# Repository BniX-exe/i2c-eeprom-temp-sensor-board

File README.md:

I2C EEPROM & Sensor Board
A custom 2-layer PCB designed in KiCad, integrating I²C-based memory, temperature sensing, elapsed time recording, and power regulation.
Overview
This project demonstrates schematic design, component selection, PCB layout, and integration of multiple I²C peripherals on a compact board.
The PCB was recreated as a personal portfolio project based on hardware design experience gained during an engineering internship.
Hardware Components
Component
Description
AT24C501
I²C EEPROM
TMP102
Digital temperature sensor
DS1683S+
Elapsed time recorder
AP2204K-ADJ
Adjustable LDO voltage regulator
Schottky Diode
Input reverse-current protection
LED
Alarm status indication
Design Features
	•	2-layer PCB designed using KiCad
	•	5V input and regulated 3.3V supply
	•	Shared I²C communication bus
	•	4.7kΩ I²C pull-up resistors
	•	On-board decoupling capacitors
	•	2×5 external interface connector
	•	Alarm and event signal connections
PCB Design
Schematic

PCB Layout

Design Tools
	•	KiCad — Schematic Capture
	•	KiCad PCB Editor — PCB Layout and Routing
Project Status
PCB schematic and layout completed. Physical manufacturing and hardware validation have not been documented.
Note
This repository contains a personally recreated PCB design intended for educational and portfolio purposes.

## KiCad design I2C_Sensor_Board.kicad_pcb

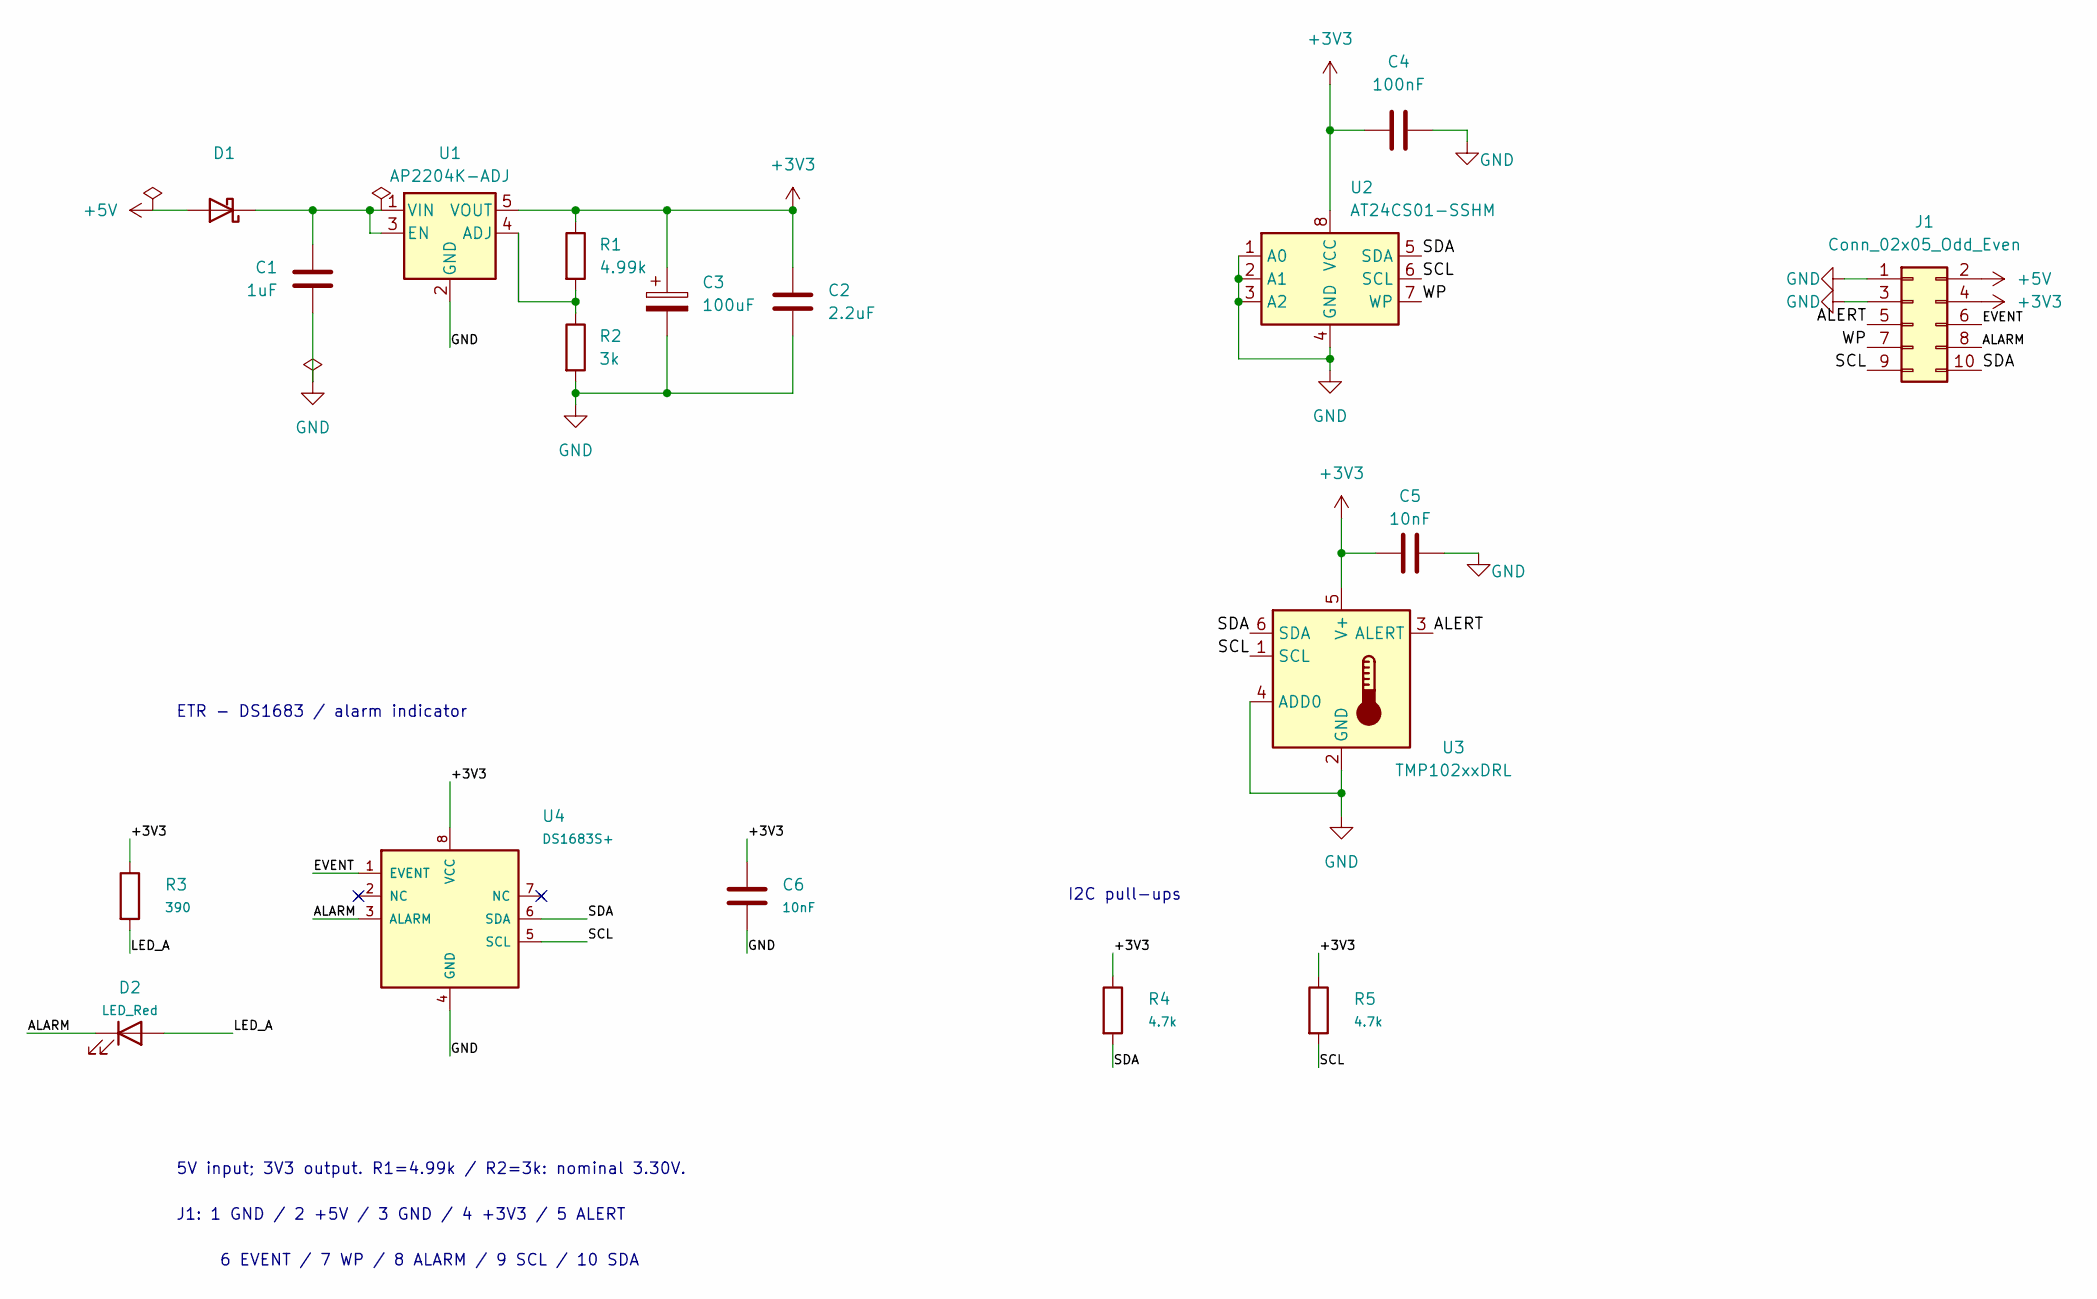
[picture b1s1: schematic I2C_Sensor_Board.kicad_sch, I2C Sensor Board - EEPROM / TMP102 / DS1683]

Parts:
C1: 1uF; C_1206_3216Metric
C2: 2.2uF; C_1206_3216Metric
C3: 100uF; CP_EIA-3528-21_Kemet-B
C4: 100nF; C_0402_1005Metric
C5, C6: 10nF; C_0402_1005Metric
D1: D_1206_3216Metric
D2: LED_Red; LED_0603_1608Metric
J1: Conn_02x05_Odd_Even; PinHeader_2x05_P2.54mm_Vertical
R1: 4.99k; R_0402_1005Metric
R2: 3k; R_0402_1005Metric
R3: 390; R_0402_1005Metric
R4, R5: 4.7k; R_0402_1005Metric
U1: AP2204K-ADJ; SOT-23-5
U2: AT24CS01-SSHM; SOIC-8_3.9x4.9mm_P1.27mm
U3: TMP102xxDRL; SOT-563
U4: DS1683S+; SOIC-8_3.9x4.9mm_P1.27mm

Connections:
+3V3: C2.1, C3.1, C4.1, C5.1, C6.1, J1.4, R1.1, R3.1, R4.1, R5.1, U1.5 (VOUT), U2.8 (VCC), U3.5 (V+), U4.8 (VCC)
+5V: D1.2 (A), J1.2
/ALARM: D2.1 (K), J1.8, U4.3 (ALARM)
/ALERT: J1.5, U3.3 (ALERT)
/EVENT: J1.6, U4.1 (EVENT)
/LED_A: D2.2 (A), R3.2
/SCL: J1.9, R5.2, U2.6 (SCL), U3.1 (SCL), U4.5 (SCL)
/SDA: J1.10, R4.2, U2.5 (SDA), U3.6 (SDA), U4.6 (SDA)
/WP: J1.7, U2.7 (WP)
GND: C1.2, C2.2, C3.2, C4.2, C5.2, C6.2, J1.1, J1.3, R2.2, U1.2 (GND), U2.1 (A0), U2.2 (A1), U2.3 (A2), U2.4 (GND), U3.2 (GND), U3.4 (ADD0), U4.4 (GND)
unnamed: C1.1, D1.1 (K), U1.1 (VIN), U1.3 (EN)
unnamed: R1.2, R2.1, U1.4 (ADJ)

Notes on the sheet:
5V input; 3V3 output. R1=4.99k / R2=3k: nominal 3.30V.
J1: 1 GND / 2 +5V / 3 GND / 4 +3V3 / 5 ALERT
6 EVENT / 7 WP / 8 ALARM / 9 SCL / 10 SDA
ETR - DS1683 / alarm indicator
I2C pull-ups

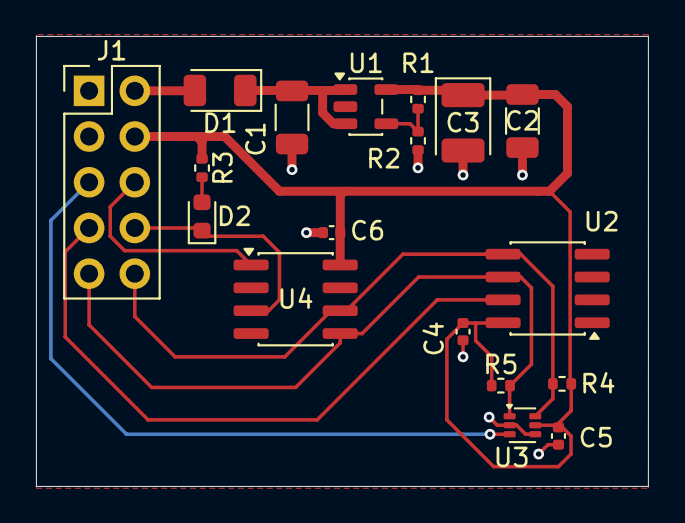
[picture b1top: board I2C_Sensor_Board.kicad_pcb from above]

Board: 2 copper layers, 34.0 x 25.0 mm, 18 parts (0 on the bottom side), 12 nets.

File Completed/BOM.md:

# Malzeme / footprint listesi

Kesin sipariş kodları ve pasiflerin gerilim/tolerans seçimi üretim öncesi tamamlanmalıdır.

| Ref | Değer / parça | KiCad footprint |
|---|---|---|
| C1 | 1uF | Capacitor_SMD:C_0402_1005Metric |
| C2 | 2.2uF | Capacitor_SMD:C_0603_1608Metric |
| C3 | 100uF | Capacitor_SMD:CP_Elec_6.3x5.4 |
| C4 | 100nF | Capacitor_SMD:C_0402_1005Metric |
| C5 | 10nF | Capacitor_SMD:C_0402_1005Metric |
| C6 | 10nF | Capacitor_SMD:C_0402_1005Metric |
| D1 | SS14 | Diode_SMD:D_SMA |
| D2 | LED_Red | LED_SMD:LED_0603_1608Metric |
| J1 | Conn_02x05_Odd_Even | Connector_PinHeader_2.54mm:PinHeader_2x05_P2.54mm_Vertical |
| R1 | 4.99k | Resistor_SMD:R_0402_1005Metric |
| R2 | 3k | Resistor_SMD:R_0402_1005Metric |
| R3 | 390 | Resistor_SMD:R_0402_1005Metric |
| R4 | 4.7k | Resistor_SMD:R_0402_1005Metric |
| R5 | 4.7k | Resistor_SMD:R_0402_1005Metric |
| R6 | 10k | Resistor_SMD:R_0402_1005Metric |
| U1 | AP2204K-ADJ | Package_TO_SOT_SMD:SOT-23-5 |
| U2 | AT24CS01-SSHM | Package_SO:SOIC-8_3.9x4.9mm_P1.27mm |
| U3 | TMP102xxDRL | Package_TO_SOT_SMD:SOT-563 |
| U4 | DS1683S+ | Package_SO:SOIC-8_3.9x4.9mm_P1.27mm |

R1 ve R2 için %1 direnç kullanın. C1 için en az 10 V; çıkış/bypass kapasitörleri için en az 6,3 V seçin. Seramik kapasitörlerin DC bias altında etkin kapasitesini kontrol edin. C3 polarize, 100 µF SMD elektrolitiktir; tam parça seçimi ve footprint uyumu bekliyor. D2 kırmızı 0603 LED olarak düşünülmüştür.

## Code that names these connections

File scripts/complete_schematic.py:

from pathlib import Path
from copy import deepcopy
import uuid
from sexp import *
ROOT=Path(__file__).resolve().parents[1]
LIB=Path('/Applications/KiCad/KiCad.app/Contents/SharedSupport/symbols')
s=parse((ROOT/'backup_original/I2C_Sensor_Board.kicad_sch').read_text())
libs=child(s,'lib_symbols'); rootid=value(child(s,'uuid')[1])
def uid(): return str(uuid.uuid4())
def add(txt):
    n=parse(txt); s.append(n); return n
def prop(n,name): return next(p for p in children(n,'property') if value(p[1])==name)
syms={value(prop(n,'Reference')[2]):n for n in children(s,'symbol')}
def loadlib(lib,name):
    n=deepcopy(next(x for x in children(parse((LIB/(lib+'.kicad_sym')).read_text()),'symbol') if value(x[1])==name))
    n[1]=q(lib+':'+name); libs.append(n)
loadlib('Device','LED'); loadlib('power','PWR_FLAG')
for ref,changes in {
    'C1':{'Value':'1uF'},
    'C2':{'Footprint':'Capacitor_SMD:C_0603_1608Metric'},
    'C3':{'Footprint':'Capacitor_SMD:CP_Elec_6.3x5.4'},
    'C5':{'Value':'10nF'},
    'R1':{'Value':'4.99k'},
    'D1':{'Value':'SS14','Footprint':'Diode_SMD:D_SMA','Datasheet':'https://www.vishay.com/docs/88746/ss12.pdf'},
    'J1':{'Footprint':'Connector_PinHeader_2.54mm:PinHeader_2x05_P2.54mm_Vertical'},
}.items():
    for key,val in changes.items(): prop(syms[ref],key)[2]=q(val)
def label(name,x,y):
    add(f'(label {q(name)} (at {x} {y} 0) (effects (font (size 1.0 1.0)) (justify left bottom)) (uuid {q(uid())}))')
def wire(x,y,xx,yy):
    add(f'(wire (pts (xy {x} {y}) (xy {xx} {yy})) (stroke (width 0) (type default)) (uuid {q(uid())}))')
def inst(lib,ref,val,fp,x,y):
    return add(f'''(symbol (lib_id {q(lib)}) (at {x} {y} 0) (unit 1)
      (in_bom yes) (on_board yes) (dnp no) (uuid {q(uid())})
      (property "Reference" {q(ref)} (at {x+3} {y-2} 0) (effects (font (size 1.27 1.27))))
      (property "Value" {q(val)} (at {x+3} {y} 0) (effects (font (size 1.0 1.0))))
      (property "Footprint" {q(fp)} (at {x} {y} 0) (effects (font (size 1.27 1.27)) (hide yes)))
      (instances (project "I2C_Sensor_Board" (path {q('/'+rootid)} (reference {q(ref)}) (unit 1)))))''')
def text(txt,x,y): add(f'(text {q(txt)} (at {x} {y} 0) (effects (font (size 1.27 1.27)) (justify left)) (uuid {q(uid())}))')
# Direct pin labels repair the disconnected regulator ground and expose ETR signals.
wire(96.52,68.58,96.52,73.66); label('GND',96.52,73.66)
label('EVENT',266.7,71.12); label('ALARM',266.7,73.66)
for i,(x,y,net) in enumerate([(63.5,58.42,'+5V'),(81.28,77.47,'GND'),(88.9,58.42,None)],1):
    inst('power:PWR_FLAG',f'#FLG0{i}','PWR_FLAG','',x,y)
# Custom DS1683 symbol: pin mapping verified against ADI data sheet, page 4.
pins=[('1','EVENT','input',-10.16,5.08,0),('2','NC','no_connect',-10.16,2.54,0),
      ('3','ALARM','open_collector',-10.16,0,0),('4','GND','power_in',0,-10.16,90),
      ('5','SCL','input',10.16,-2.54,180),('6','SDA','bidirectional',10.16,0,180),
      ('7','NC','no_connect',10.16,2.54,180),('8','VCC','power_in',0,10.16,270)]
pinstr=''.join(f'(pin {typ} line (at {x} {y} {ang}) (length 2.54) (name {q(name)} (effects (font (size 1.0 1.0)))) (number {q(num)} (effects (font (size 1.0 1.0)))))' for num,name,typ,x,y,ang in pins)
custom=parse(f'''(symbol "I2C_Sensor_Board:DS1683S+" (pin_names (offset 0.8)) (in_bom yes) (on_board yes)
  (property "Reference" "U" (at 0 0 0) (effects (font (size 1.27 1.27))))
  (property "Value" "DS1683S+" (at 0 0 0) (effects (font (size 1.27 1.27))))
  (property "Footprint" "Package_SO:SOIC-8_3.9x4.9mm_P1.27mm" (at 0 0 0) (effects (font (size 1.27 1.27)) (hide yes)))
  (property "Datasheet" "https://www.analog.com/media/en/technical-documentation/data-sheets/DS1683.pdf" (at 0 0 0) (effects (font (size 1.27 1.27)) (hide yes)))
  (symbol "DS1683S+_0_1" (rectangle (start -7.62 7.62) (end 7.62 -7.62) (stroke (width 0.254) (type default)) (fill (type background))))
  (symbol "DS1683S+_1_1" {pinstr}))''')
libs.append(custom)
external=deepcopy(custom); external[1]=q('DS1683S+')
(ROOT/'I2C_Sensor_Board.kicad_sym').write_text(dump(['kicad_symbol_lib',['version','20241209'],['generator',q('kicad_symbol_editor')],external])+'\n')
(ROOT/'sym-lib-table').write_text('(sym_lib_table (version 7) (lib (name "I2C_Sensor_Board") (type "KiCad") (uri "${KIPRJMOD}/I2C_Sensor_Board.kicad_sym") (options "") (descr "DS1683, datasheet pin mapping")))\n')
inst('I2C_Sensor_Board:DS1683S+','U4','DS1683S+','Package_SO:SOIC-8_3.9x4.9mm_P1.27mm',96.52,137.16)
for num,name,typ,px,py,angle in pins:
    x,y=round(96.52+px,4),round(137.16-py,4)
    if typ=='no_connect': add(f'(no_connect (at {x} {y}) (uuid {q(uid())}))')
    else:
        nx=x-5.08 if px<0 else x+5.08 if px>0 else x
        ny=y-5.08 if py>7.62 else y+5.08 if py<-7.62 else y
        wire(x,y,round(nx,4),round(ny,4)); label('+3V3' if name=='VCC' else name,round(nx,4),round(ny,4))
inst('Device:C','C6','10nF','Capacitor_SMD:C_0402_1005Metric',129.54,134.62)
label('+3V3',129.54,130.81); label('GND',129.54,138.43)
text('ETR - DS1683 / alarm indicator',66.04,114.3)
for ref,val,x,top,bottom in [('R3','390',60.96,'+3V3','LED_A'),('R4','4.7k',170.18,'+3V3','SDA'),('R5','4.7k',193.04,'+3V3','SCL'),('R6','10k',215.9,'+3V3','ALERT')]:
    inst('Device:R',ref,val,'Resistor_SMD:R_0402_1005Metric',x,134.62)
    label(top,x,130.81); label(bottom,x,138.43)
inst('Device:LED','D2','LED_Red','LED_SMD:LED_0603_1608Metric',60.96,149.86)
label('ALARM',57.15,149.86); label('LED_A',64.77,149.86)
text('I2C pull-ups + ALERT pull-up',165.1,121.92)
text('5V input; 3V3 output. R1=4.99k / R2=3k: nominal 3.30V.',66.04,165.1)
text('J1: 1 GND / 2 +5V / 3 GND / 4 +3V3 / 5 ALERT',66.04,170.18)
text('     6 EVENT / 7 WP / 8 ALARM / 9 SCL / 10 SDA',66.04,175.26)
(ROOT/'I2C_Sensor_Board.kicad_sch').write_text(dump(s)+'\n')
print('Completed schematic and project-local DS1683 library.')
